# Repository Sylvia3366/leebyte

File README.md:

# LEEBYTE™

[ONSHAPE CAD](https://cad.onshape.com/documents/775b1919785149165ef0f27a/w/a0b05a09ec9f946b8b8a4a30/e/c002d06697f726d420ef8c8a?renderMode=0&uiState=6a315a62f65bd0542a2cae44)
-

# What is it?
LEEBYTE is a mischevious tamagotchi pet bunny you can play with, take care of, bully, or put in your pocket and forget about for the next twenty years! It features a 2-axis joystick, three Jureumi themed buttons, and a temperature sensor that will cause LEEBYTE to have different reactions based on your enviornment :)!

# Why did I make it?
I made this project as a start point to my hardware journey! While starting with an odd, rabbit head PCB may not have been the best idea, it challenged me a lot. 

My main motivation after seeing the guide for it on Fallout website was the existing Leebit Tamagotchi [(See here!)](https://kplaceshop.com/products/stray-kids-skzoo-tamagotchi-case-set?variant=51409921999166). It's way out of my budget though, so I thought this would be the perfect chance for me to design one myself, and customize it to my own liking! Additionally, I've been wanting to get into pixel art for a while, and this project let me experiment with drawing so many different expressions and actions.

# How does it work?
LEEBYTE is unlike the usual 3-button tamagotchi pet; he can move! Using the joystick, you can take LEEBYTE on adventures and perhaps, you'll even find some cool treasures along the way... 

Like most tamagotchi, LEEBYTE also comes with 3 Jureumi themed buttons that can be pressed to feed him, play with him, or put him to sleep. Pressing two buttons at once can have some effect too :). When playing with LEEBYTE, he enjoys hula hooping, jump roping, or (if he's in the mood) you can even play a short game of some good ol' Tic-Tac-Toe. 

He's also able to detect the temperature of your enviornment. Make sure you keep him warm during the freezing winters and next to a blasting AC during the blazing summers! Otherwise, LEEBYTE might leave you...

# Designing the PCB
PCB designed on KiCad!
-

Case designed and assembled on OnShape!
-

Rendered on Fusion360!
-

# Bill of Materials
| Name | Qty | Unit | Price (USD) | Total (USD) | MOQ | MOQ Price (USD) | Source |
| :--- | :---: | :---: | ---: | ---: | ---: | ---: | :--- |
| Seeed Studio XIAO ESP32 C3 | 1 | pcs | 11.14 | 11.14 | 1 | 11.14 | [Link](https://www.aliexpress.us/item/3256808047100037.html) |
| PSP 2-Axis Analog Thumb Joystick | 1 | pcs | 3.50 | 3.50 | 1 | 3.50 | [Link](https://www.adafruit.com/product/444) |
| 0.96 inch OLED Display 128x64 | 1 | pcs | 1.91 | 1.91 | 1 | 1.91 | [Link](https://www.aliexpress.us/item/2251832337475453.html) |
| Right Angle Slide Switch | 1 | pcs | 1.00 | 1.00 | 1 | 1.00 | [Link](https://www.alibaba.com/product-detail/Brand-New-Original-MST-12D18G4-SPDT_1601682630920.html) |
| 4.7k Resistor | 1 | pcs | 0.01 | 0.01 | 100 | 1.47 | [Link](https://www.aliexpress.us/item/2251832130817202.html) |
| Temperature Sensor (DS18B20) | 1 | pcs | 0.48 | 0.48 | 5 | 2.42 | [Link](https://www.aliexpress.us/item/3256808767131467.html) |
| Piezo Buzzer | 1 | pcs | 0.50 | 0.50 | 10 | 5.02 | [Link](https://www.aliexpress.us/item/3256810135642750.html) |
| Tactile Switch | 3 | pcs | 0.23 | 0.68 | 10 | 2.25 | [Link](https://www.aliexpress.us/item/3256807067168626.html) |
| M1.6 5mm Screws | 7 | pcs | 0.03 | 0.21 | 50 | 1.56 | [Link](https://www.aliexpress.us/item/2251832785290389.html) |
| M3 8mm Screws | 3 | pcs | 0.04 | 0.13 | 50 | 2.09 | [Link](https://www.aliexpress.us/item/2251832785290389.html) |
| M2 5mm Standoff | 2 | pcs | 0.15 | 0.30 | 20 | 2.94 | [Link](https://www.aliexpress.us/item/3256804631738035.html) |
| M2 Hex Nut | 2 | pcs | 0.07 | 0.14 | 50 | 3.38 | [Link](https://www.aliexpress.us/item/3256806284464354.html) |
| Battery | 1 | pcs | 5.16 | 5.16 | 1 | 5.16 | [Link](https://www.aliexpress.us/item/3256808658204287.html) |
| PCB | 1 | pcs | 0.40 | 0.40 | 5 | 2.00 | [Link](https://jlcpcb.com) |
| PLA 3D Printed Case | 1 | pcs | - | - | - | - | - |
| **Total** | **27** | **-** | **-** | **25.56** | **-** | **45.84** | **-** |

# Build & Assembly
Required Tools
-
1. Solder
2. Soldering iron
3. Tweezers
4. Screwdriver for M3/M2/M1.6 screws
5. Computer w. a USB port
6. 3D printer

Assembly
-
1. Solder all parts onto the PCB.
2. Secure the button caps onto the tact switches.
3. Secure the joystick with 2 M2 5mm screws, M2 standoffs, and M2 hex nuts.
4. Place the battery in the open part below the bottom case.
5. Place PCB into the bottom case and wire to battery.
6. Secure the PCB with 3 M3 screws.
7. Place the top case over the bottom and secure with the M1.6 screws.
8. Use Arduino IDE for the firmware.
9. Connect the ESP32 to your computer via USB-C to upload code.
10. Upload firmware.
11. Test the OLED display and test the joystick inputs.

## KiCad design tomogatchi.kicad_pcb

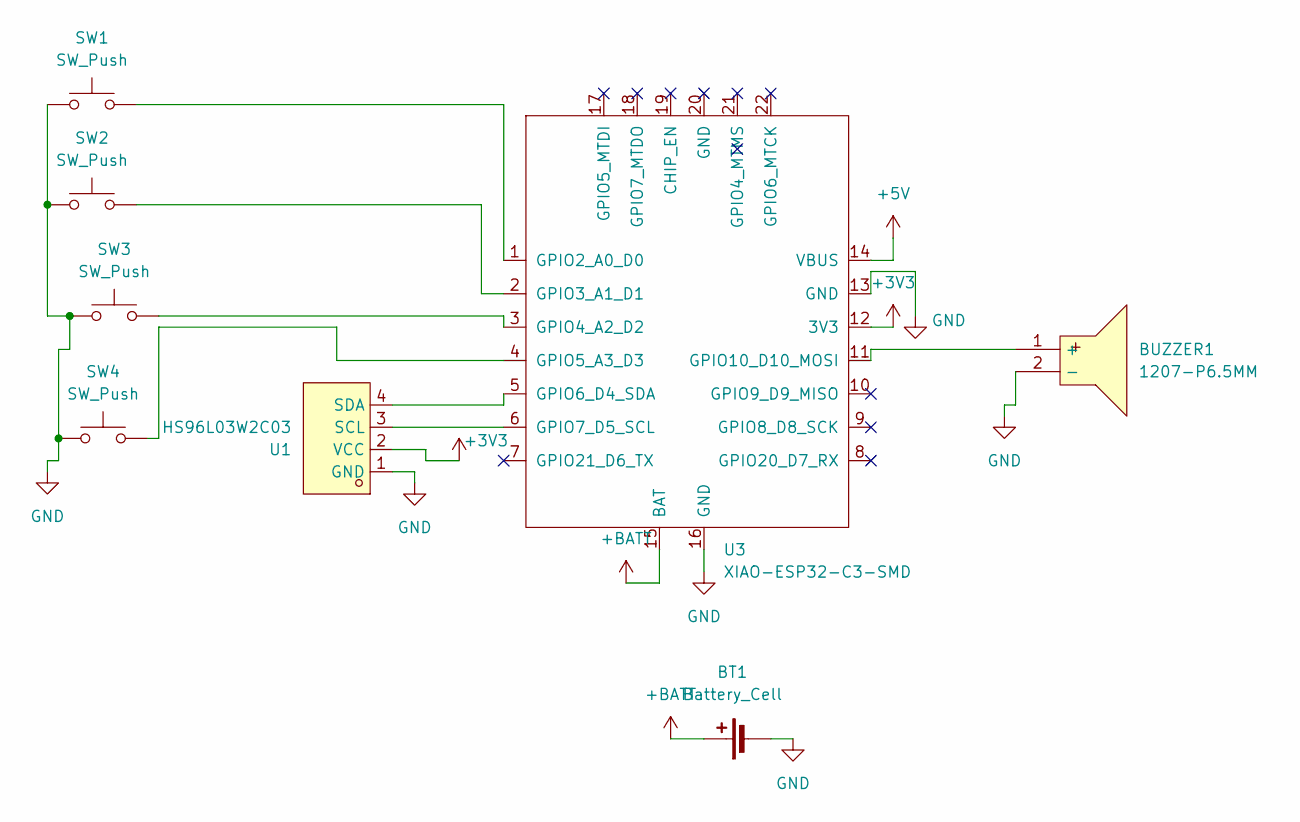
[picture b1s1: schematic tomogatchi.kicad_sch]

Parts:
BT1: Battery_Cell; PinHeader_1x02_P2.54mm_Vertical
BUZZER1: 1207-P6.5MM; BUZ-TH_BD12.5-P6.50-D1.4; MPN 1207-P6.5MM; LCSC Part C49246964
SW1, SW2, SW3, SW4: SW_Push; SW-TH_4P-L4.5-W4.5-P3.00-LS4.8
U1: HS96L03W2C03; OLED-TH_L27.8-W27.2-P2.54_C9900033791; MPN HS96L03W2C03; LCSC Part C5248080
U3: XIAO-ESP32-C3-SMD; XIAO-ESP32-C3-DIP-SMD

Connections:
+3V3: U1.2 (VCC), U3.12 (3V3)
+5V: U3.14 (VBUS)
+BATT: BT1.1 (+), U3.15 (BAT)
GND: BT1.2 (-), BUZZER1.2 (-), SW1.1, SW2.1, SW3.1, SW4.1, U1.1 (GND), U3.13 (GND), U3.16 (GND)
unnamed: BUZZER1.1 (+), U3.11 (GPIO10_D10_MOSI)
unnamed: U1.3 (SCL), U3.6 (GPIO7_D5_SCL)
unnamed: U1.4 (SDA), U3.5 (GPIO6_D4_SDA)
unnamed: SW1.2, U3.1 (GPIO2_A0_D0)
unnamed: SW2.2, U3.2 (GPIO3_A1_D1)
unnamed: SW3.2, U3.3 (GPIO4_A2_D2)
unnamed: SW4.2, U3.4 (GPIO5_A3_D3)

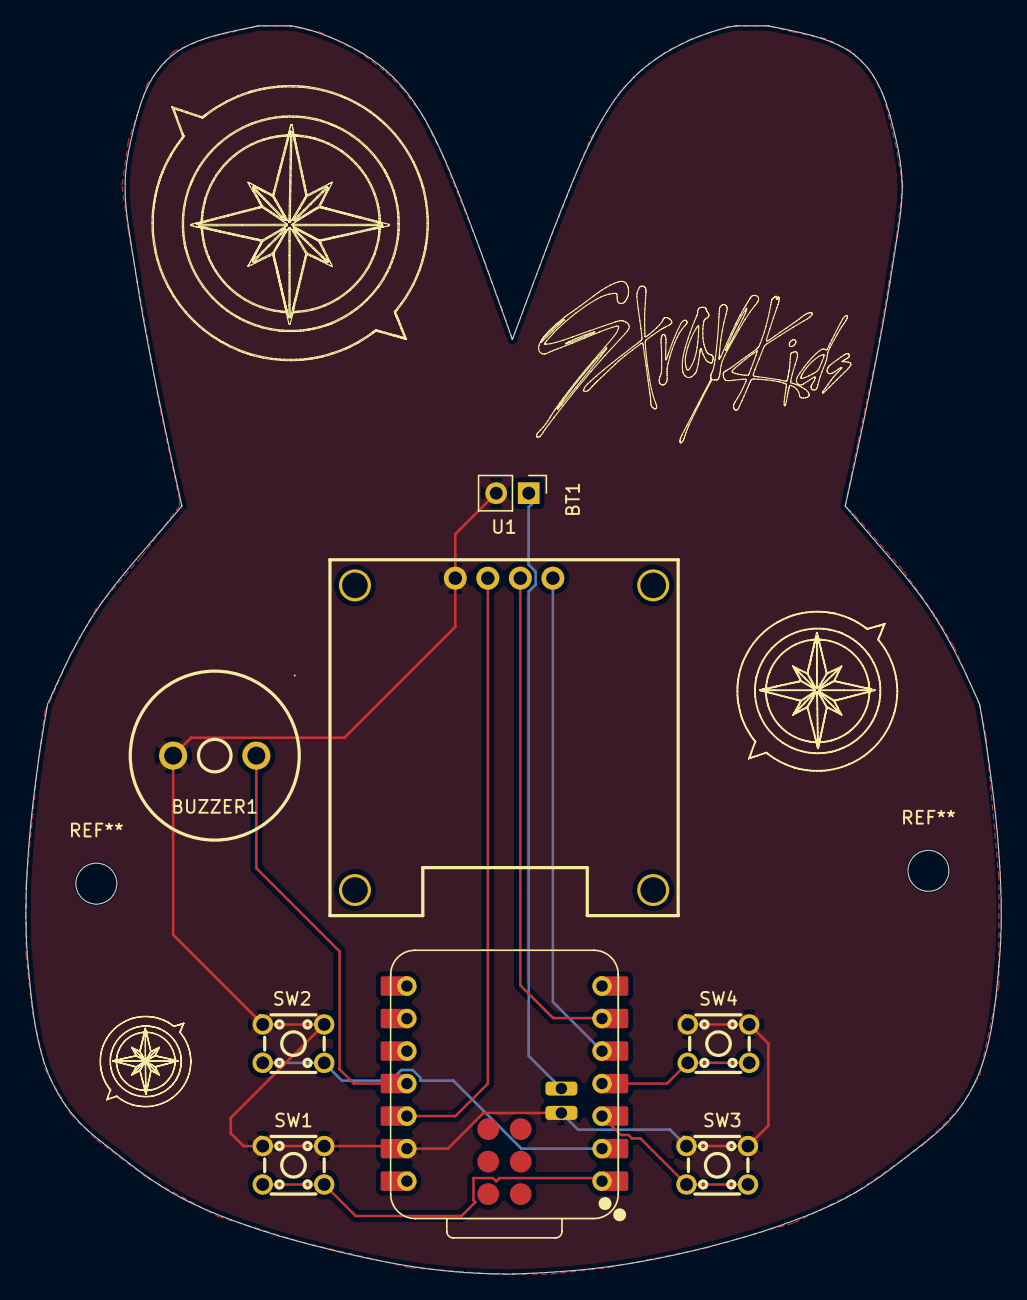
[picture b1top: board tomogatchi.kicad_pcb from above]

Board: 2 copper layers, 76.2 x 97.5 mm, 8 parts (0 on the bottom side), 10 nets.

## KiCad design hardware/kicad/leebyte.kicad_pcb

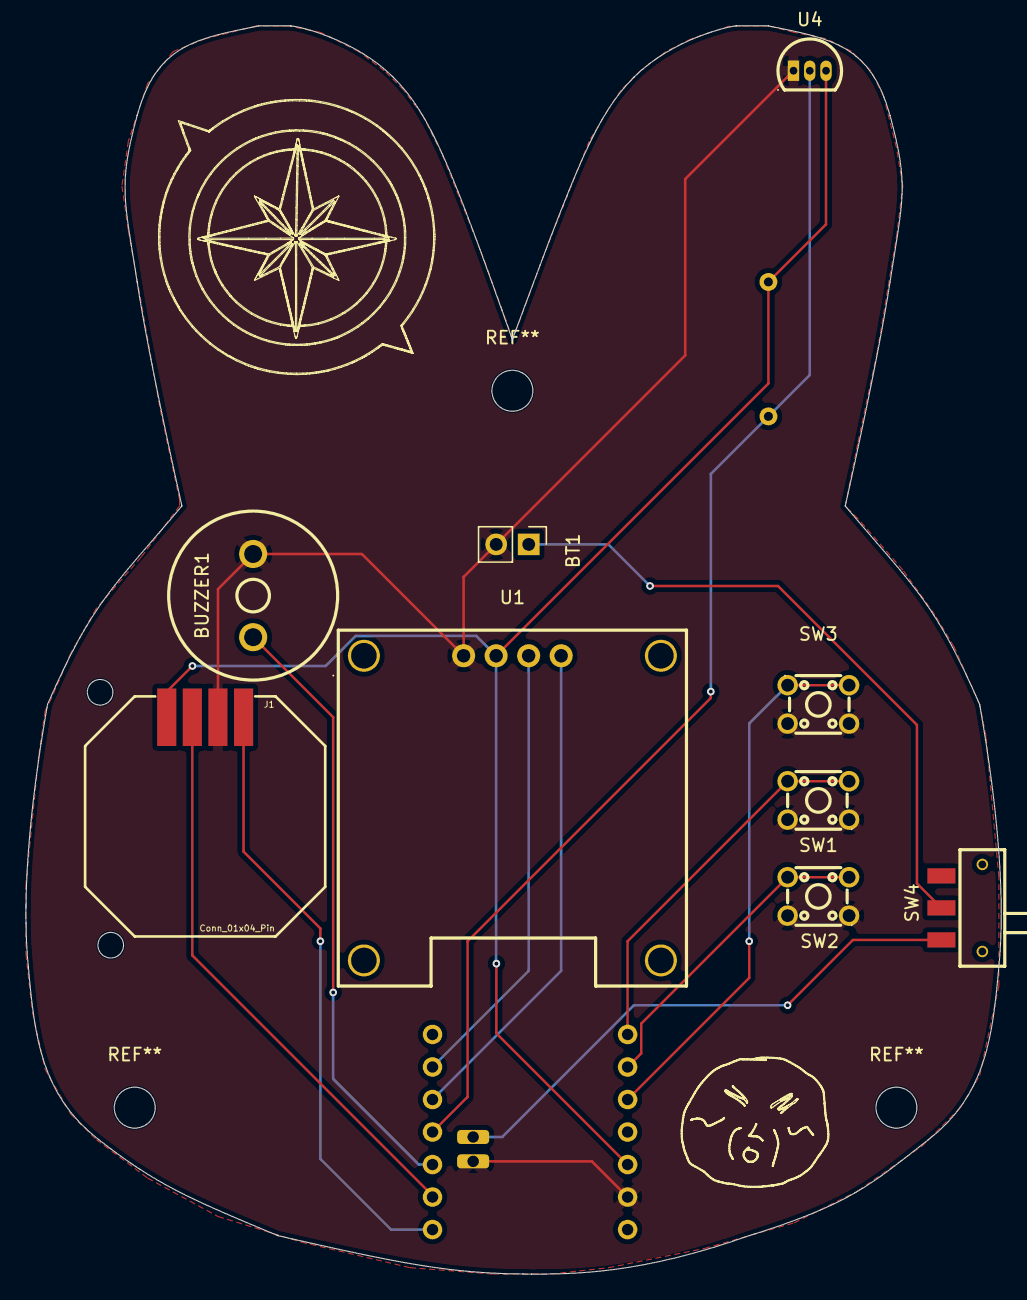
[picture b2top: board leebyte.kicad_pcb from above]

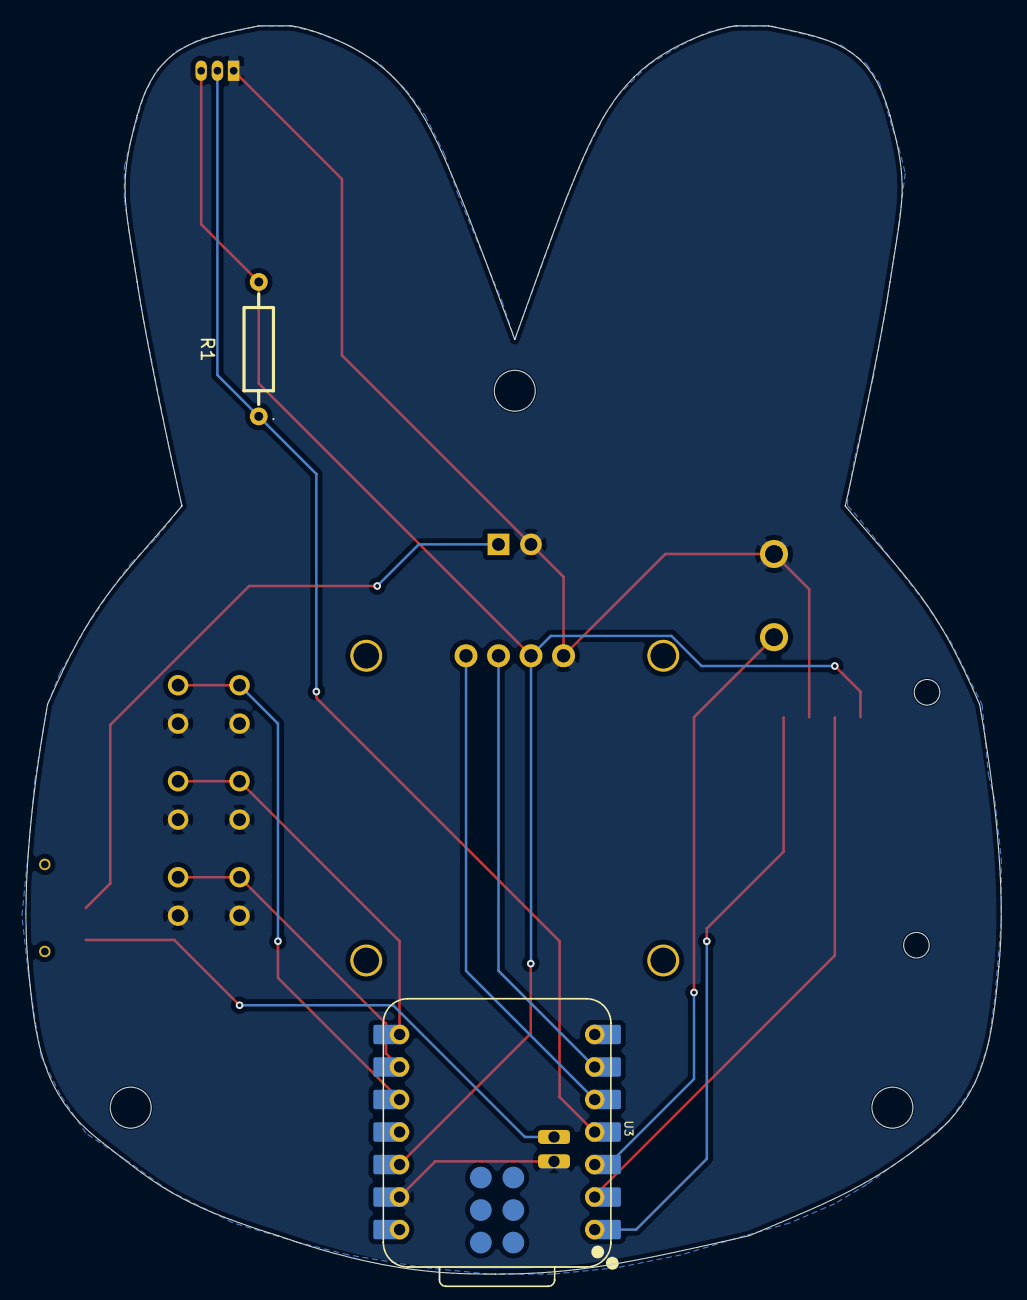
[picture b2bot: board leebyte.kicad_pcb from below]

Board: 2 copper layers, 76.2 x 97.5 mm, 11 parts (2 on the bottom side), 13 nets.

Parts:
BT1: Battery_Cell; PinHeader_1x02_P2.54mm_Vertical
BUZZER1: 1207-P6.5MM; BUZ-TH_BD12.5-P6.50-D1.4
J1: Conn_01x04_Pin; JOYSTICK-PSP1000
R1: 4.7k; RES-TH_BD2.3-L6.5-P10.50-D0.5
SW1, SW2, SW3: SW_Push; SW-TH_4P-L4.5-W4.5-P3.00-LS4.8
SW4: MST-12D18G4 SPDT SLIDE SWITCH; SW-SMD_MST-12D18G4-SPDT-SLIDE-SWITCH
U1: HS96L03W2C03; OLED-TH_L27.8-W27.2-P2.54_C9900033791
U3: XIAO-ESP32-C3-SMD; XIAO-ESP32-C3-DIP-SMD
U4: DS18B20; TO-92-3_L4.9-W3.7-P1.27-L

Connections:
+3V3: J1.4, R1.2, U1.2 (VCC), U3.12 (3V3), U4.3 (V_{DD})
+BATT: SW4.1, U3.15 (BAT)
GND: BT1.2 (-), BUZZER1.2 (-), J1.2, SW1.2, SW2.2, SW3.2, U1.1 (GND), U3.13 (GND), U3.16 (GND), U4.1 (GND)
unnamed: BT1.1 (+), SW4.2
unnamed: BUZZER1.1 (+), U3.3 (GPIO4_A2_D2)
unnamed: J1.1, U3.1 (GPIO2_A0_D0)
unnamed: J1.3, U3.2 (GPIO3_A1_D1)
unnamed: U1.3 (SCL), U3.6 (GPIO7_D5_SCL)
unnamed: U1.4 (SDA), U3.5 (GPIO6_D4_SDA)
unnamed: R1.1, U3.4 (GPIO5_A3_D3), U4.2 (DQ)
unnamed: SW2.1, U3.9 (GPIO8_D8_SCK)
unnamed: SW3.1, U3.10 (GPIO9_D9_MISO)
unnamed: SW1.1, U3.8 (GPIO20_D7_RX)

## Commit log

2026-06-15 Rename Copy of fallout_zine_template.pdf.pdf to zine
2026-06-16 Create leebyte_zine (w.margins)
2026-06-16 Rename leebyte_render.png to leebyte_RENDER.png
2026-06-16 Rename leebyte_zine (w. margins).pdf to leebyte_ZINE(w. margins).pdf
2026-06-16 Rename leebyte_zine (wo. margins).pdf to leebyte_ZINE (wo. margins).pdf
2026-06-16 Rename leebyte_ZINE(w. margins).pdf to leebyte_ZINE (w. margins).pdf
2026-06-16 Rename GERBERS2.zip to gerbers.zip
2026-06-16 Rename tamagotchi 2-B_Cu.gbr to leebyte-B_Cu.gbr
2026-06-16 Rename tamagotchi 2-B_Mask.gbr to leebyte-B_Mask.gbr
2026-06-16 Rename tamagotchi 2-B_Paste.gbr to leebyte-B_Paste.gbr
2026-06-16 Rename tamagotchi 2-B_Silkscreen.gbr to leebyte-B_Silkscreen.gbr
2026-06-16 Rename tamagotchi 2-Edge_Cuts.gbr to leebyte-Edge_Cuts.gbr
2026-06-16 Rename tamagotchi 2-F_Cu.gbr to leebyte-F_Cu.gbr
2026-06-16 Rename tamagotchi 2-F_Mask.gbr to leebyte-F_Mask.gbr
2026-06-16 Rename tamagotchi 2-F_Paste.gbr to leebyte-F_Paste.gbr
2026-06-16 Rename tamagotchi 2-F_Silkscreen.gbr to leebyte-F_Silkscreen.gbr
2026-06-16 Rename tamagotchi 2-PTH.drl to leebyte-PTH.drl
2026-06-16 Rename tamagotchi 2-job.gbrjob to leebyte-job.gbrjob
2026-06-16 Rename tamagotchi 2-NPTH.drl to leebyte-NPTH.drl
2026-06-16 Rename tamagotchi 2.kicad_pcb to leebyte.kicad_pcb
2026-06-16 Rename tamagotchi 2.kicad_pro to leebyte.kicad_pro
2026-06-16 Rename tamagotchi 2.kicad_sch to leebyte.kicad_sch
2026-06-16 Rename exports/gerbers.zip to kicad/exports/gerbers.zip
2026-06-16 Create exports
2026-06-16 Create gerbers
2026-06-16 Create 0.96" OLED 128x64
2026-06-16 Rename Áã¼þ11 (1).step to DS18B20 model.step
2026-06-16 Rename BUZ-TH_BD12.5-H7.0-P6.5 (1).step to Buzzer model.step
2026-06-16 Rename OLED-TH_L27.8-W27.2-P2.54_C9900033791 (1).step to 128x64 OLED model.step
2026-06-16 Rename RES-TH_D2.3-L6.5-P10.50 (1).step to 4.7k res model.step
2026-06-16 Rename SW-TH_4P-L4.5-W4.5-P3.00-LS4.8 (1).step to Tact Switch model.step
2026-06-16 Rename Slide Switch.step to Slide Switch model.step
2026-06-16 Rename tamagotchipcb123 1 - Hex socket head cap screw M3x0.50 x 8.step to M3x0.5mm 8mm Screw model.step
2026-06-16 Rename tamagotchipcb123 1 - PZ Pan head screw M1.6x0.35 x 8.step to M1.6x0.35mm 6mm Screw model.step
2026-06-16 Rename case/CAD/128x64 OLED model.step to case/CAD/128x64 OLED Model/model
2026-06-16 Rename case/CAD/4.7k res model.step to case/CAD/4.7k Resistor Model/model
2026-06-16 Rename case/CAD/Buzzer model.step to case/CAD/Buzzer Model/model
2026-06-16 Rename case/CAD/DS18B20 model.step to case/CAD/DS18B20 Model/mode
2026-06-16 Rename case/CAD/M1.6x0.35mm 6mm Screw model.step to case/CAD/M1.6x0.35mm 6mm Screw Model/mod
2026-06-16 Rename case/CAD/M3x0.5mm 8mm Screw model.step to case/CAD/M3x0.5mm 8mm Screw Model/m
2026-06-16 Rename case/CAD/Slide Switch model.step to case/CAD/Slide Switch Model/m
2026-06-16 Rename case/CAD/Standoff m-f - M2 x 5 across flats 4mm (3).step to case/CAD/M2 4mm Standoff Model/m
2026-06-16 Rename Tact Switch model.step to Tact Switch Model
2026-06-16 Create Tact Switch Model
2026-06-16 Create model
2026-06-16 Rename Hex nut style 1 grade A & B M2x0.4.step to Hex nut style 1 grade A & B M2x0.4.step
2026-06-16 Rename Hex nut style 1 grade A & B M2x0.4.stl to Hex nut style 1 grade A & B M2x0.4.stl
2026-06-16 Create mode
2026-06-16 Create hi
2026-06-16 Create mode;
2026-06-16 Rename Tamagotchi.ino.ino to Tamagotchi.ino
